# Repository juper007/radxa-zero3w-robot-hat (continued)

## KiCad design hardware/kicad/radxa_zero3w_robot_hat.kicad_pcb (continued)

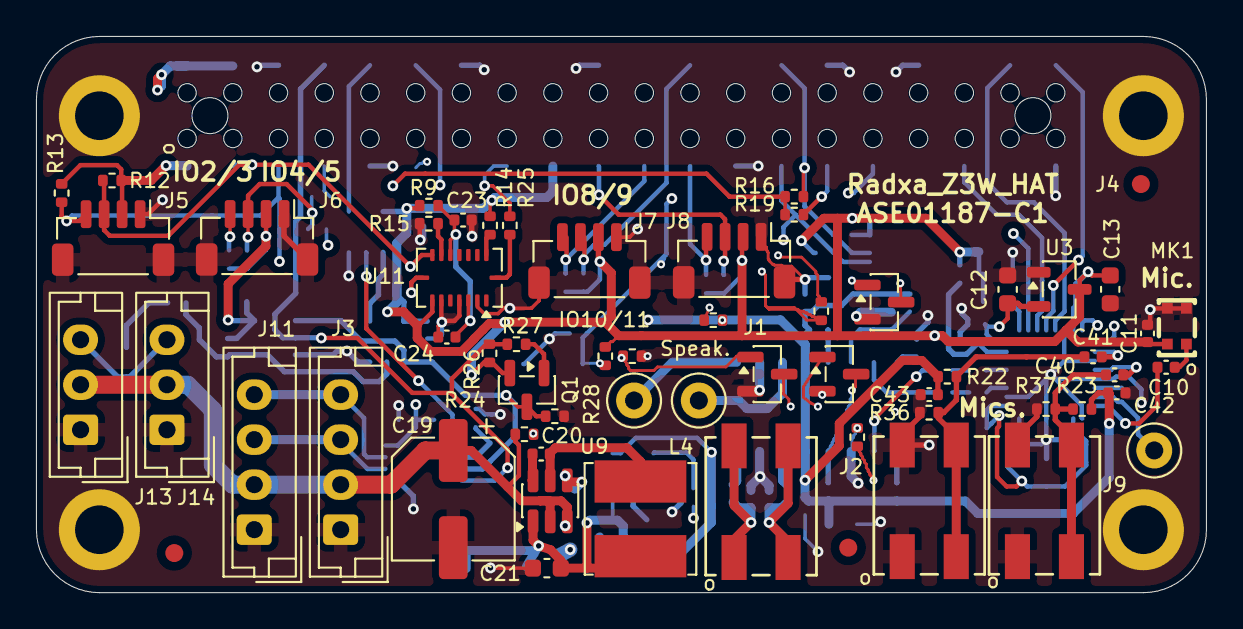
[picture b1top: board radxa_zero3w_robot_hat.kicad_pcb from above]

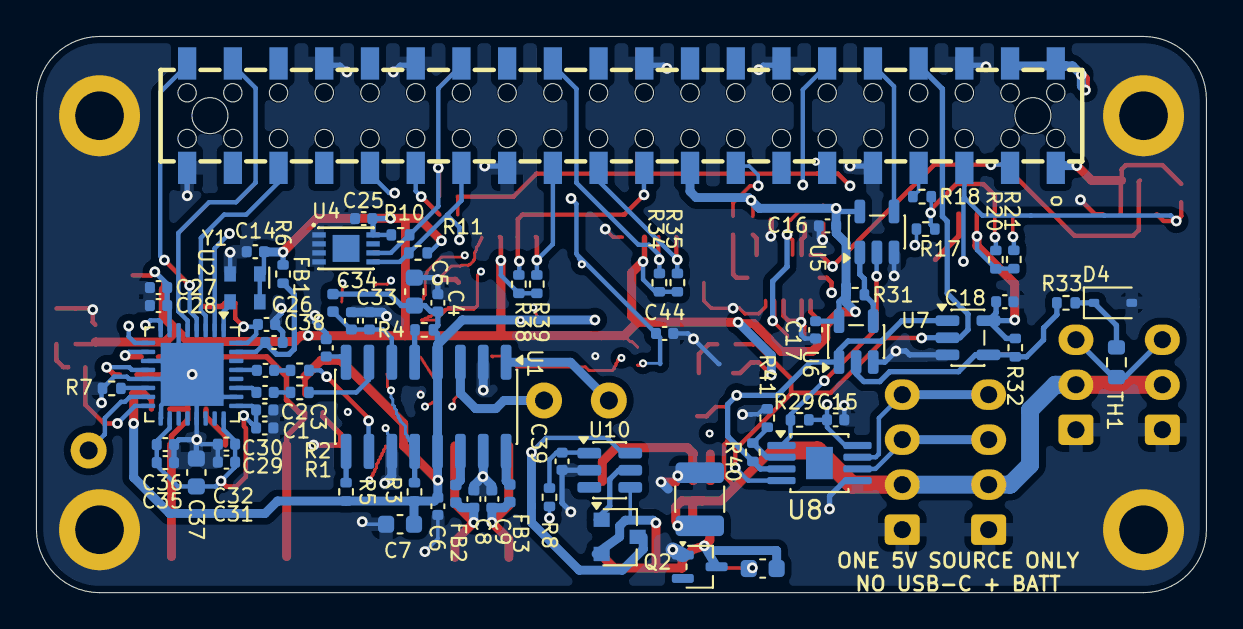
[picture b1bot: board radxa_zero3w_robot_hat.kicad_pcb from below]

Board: 4 copper layers, 65.0 x 30.9 mm, 133 parts (73 on the bottom side), 75 nets.

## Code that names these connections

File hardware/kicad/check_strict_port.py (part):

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    """Exact host-referenced presence detector and high-Z/default-OFF amp topology.

    Q3 inverts battery presence into a 3V3 pull-up, never a raw battery input.
    R46 holds Q5 off at high-Z; R44 then turns Q4 on, clamping AMP_SHDN low.
    This is a connectivity/identity contract, not an analog or boot-time proof.
    """
    root = ET.parse(netlist).getroot()
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            pins[key] = net.get("name")
    exact = {
        "BAT_BASE": {("R24", "1"), ("R42", "1"), ("Q3", "1")},
        "/Schematic/Audio/GPIO3_B4_P31": {("Q3", "3"), ("R43", "1"), ("C44", "1"), ("J4", "31")},
        "AMP_SHDN": {("R3", "1"), ("Q4", "3"), ("U1", "12")},
        "AMP_INHIBIT": {("R44", "1"), ("Q4", "1"), ("Q5", "3")},
        "AMP_BASE": {("R45", "1"), ("Q5", "1"), ("R46", "1")},
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                kind = "input" if ref.startswith("Q") and pin == "1" else "passive"
                if (node.get("pinfunction", ""), node.get("pintype", "")) != (function, kind):
                    fail(f"Stage 2 {ref}.{pin} electrical pin tuple changed")
    j11 = nets["AMP_ENABLE"].find("node[@ref='J4'][@pin='11']")
    if (j11.get("pinfunction"), j11.get("pintype")) != ("Pin_11_11", "passive"):
        fail("Stage 2 J4.11 must be a connected passive header pin")
    supply = {"+BATT": {("R24", "2")}, "+3V3": {("R43", "2")},
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        nodes = [node for node in nodes if node[0] not in new_refs]
        if name == "BAT_BASE":
            nodes.remove(("R24", "1", "", "passive"))
        if name == "/Schematic/Audio/GPIO3_B4_P31":
            nodes.extend([("R24", "1", "", "passive"), ("D2", "1", "K_1", "passive")])
        if name == "GND":
            nodes.append(("D2", "2", "A_2", "passive"))
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        4: "+5V",
        5: "I2C3_SCL_M0",
        6: "GND",
        7: "GPIO3_C4_P7",
        8: "UART2_TX_M0",
        9: "GND",
        10: "UART2_RX_M0",
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        12: "I2S3_SCLK_M0",
        13: "unconnected-(J4-Pin_13-Pad13)",
        14: "GND",
        15: "GPIO3_B0_P15",
        16: "unconnected-(J4-Pin_16-Pad16)",
        17: "+3V3",
        18: "unconnected-(J4-Pin_18-Pad18)",
        19: "GPIO4_C3_P19",
        20: "GND",
        21: "GPIO4_C5_P21",
        22: "unconnected-(J4-Pin_22-Pad22)",
        23: "GPIO4_C2_P23",
        24: "GPIO4_C6_P24",
        25: "GND",
        26: "unconnected-(J4-Pin_26-Pad26)",
        27: "I2C4_SDA_M0_P27",
        28: "I2C4_SCL_M0_P28",
        29: "GPIO3_B3_P29",
        30: "GND",
        31: "GPIO3_B4_P31",
        32: "unconnected-(J4-Pin_32-Pad32)",
        33: "unconnected-(J4-Pin_33-Pad33)",
        34: "GND",
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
